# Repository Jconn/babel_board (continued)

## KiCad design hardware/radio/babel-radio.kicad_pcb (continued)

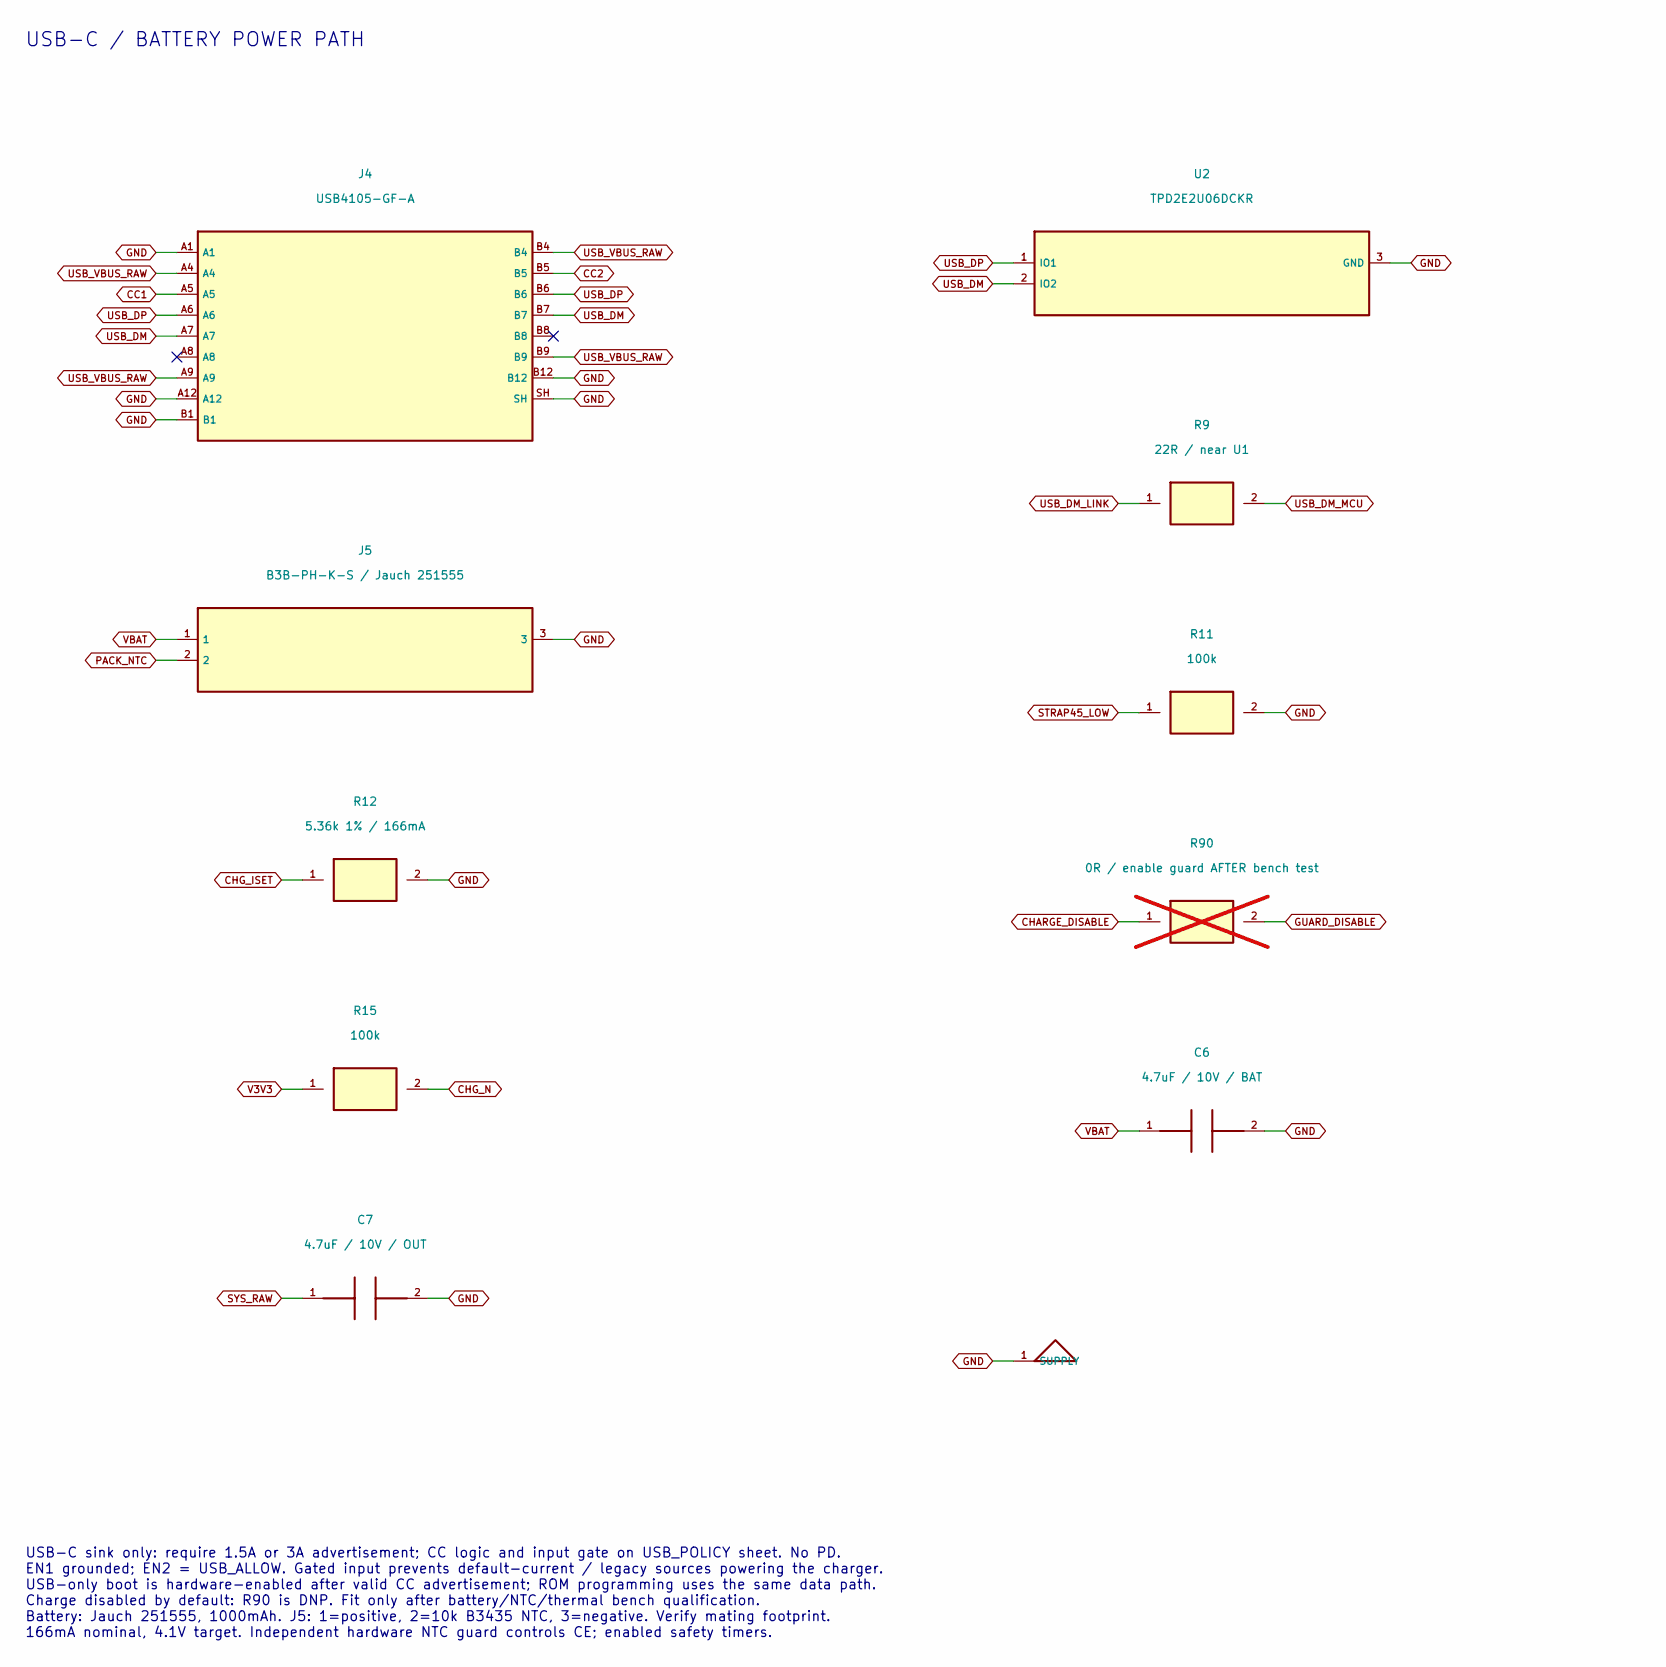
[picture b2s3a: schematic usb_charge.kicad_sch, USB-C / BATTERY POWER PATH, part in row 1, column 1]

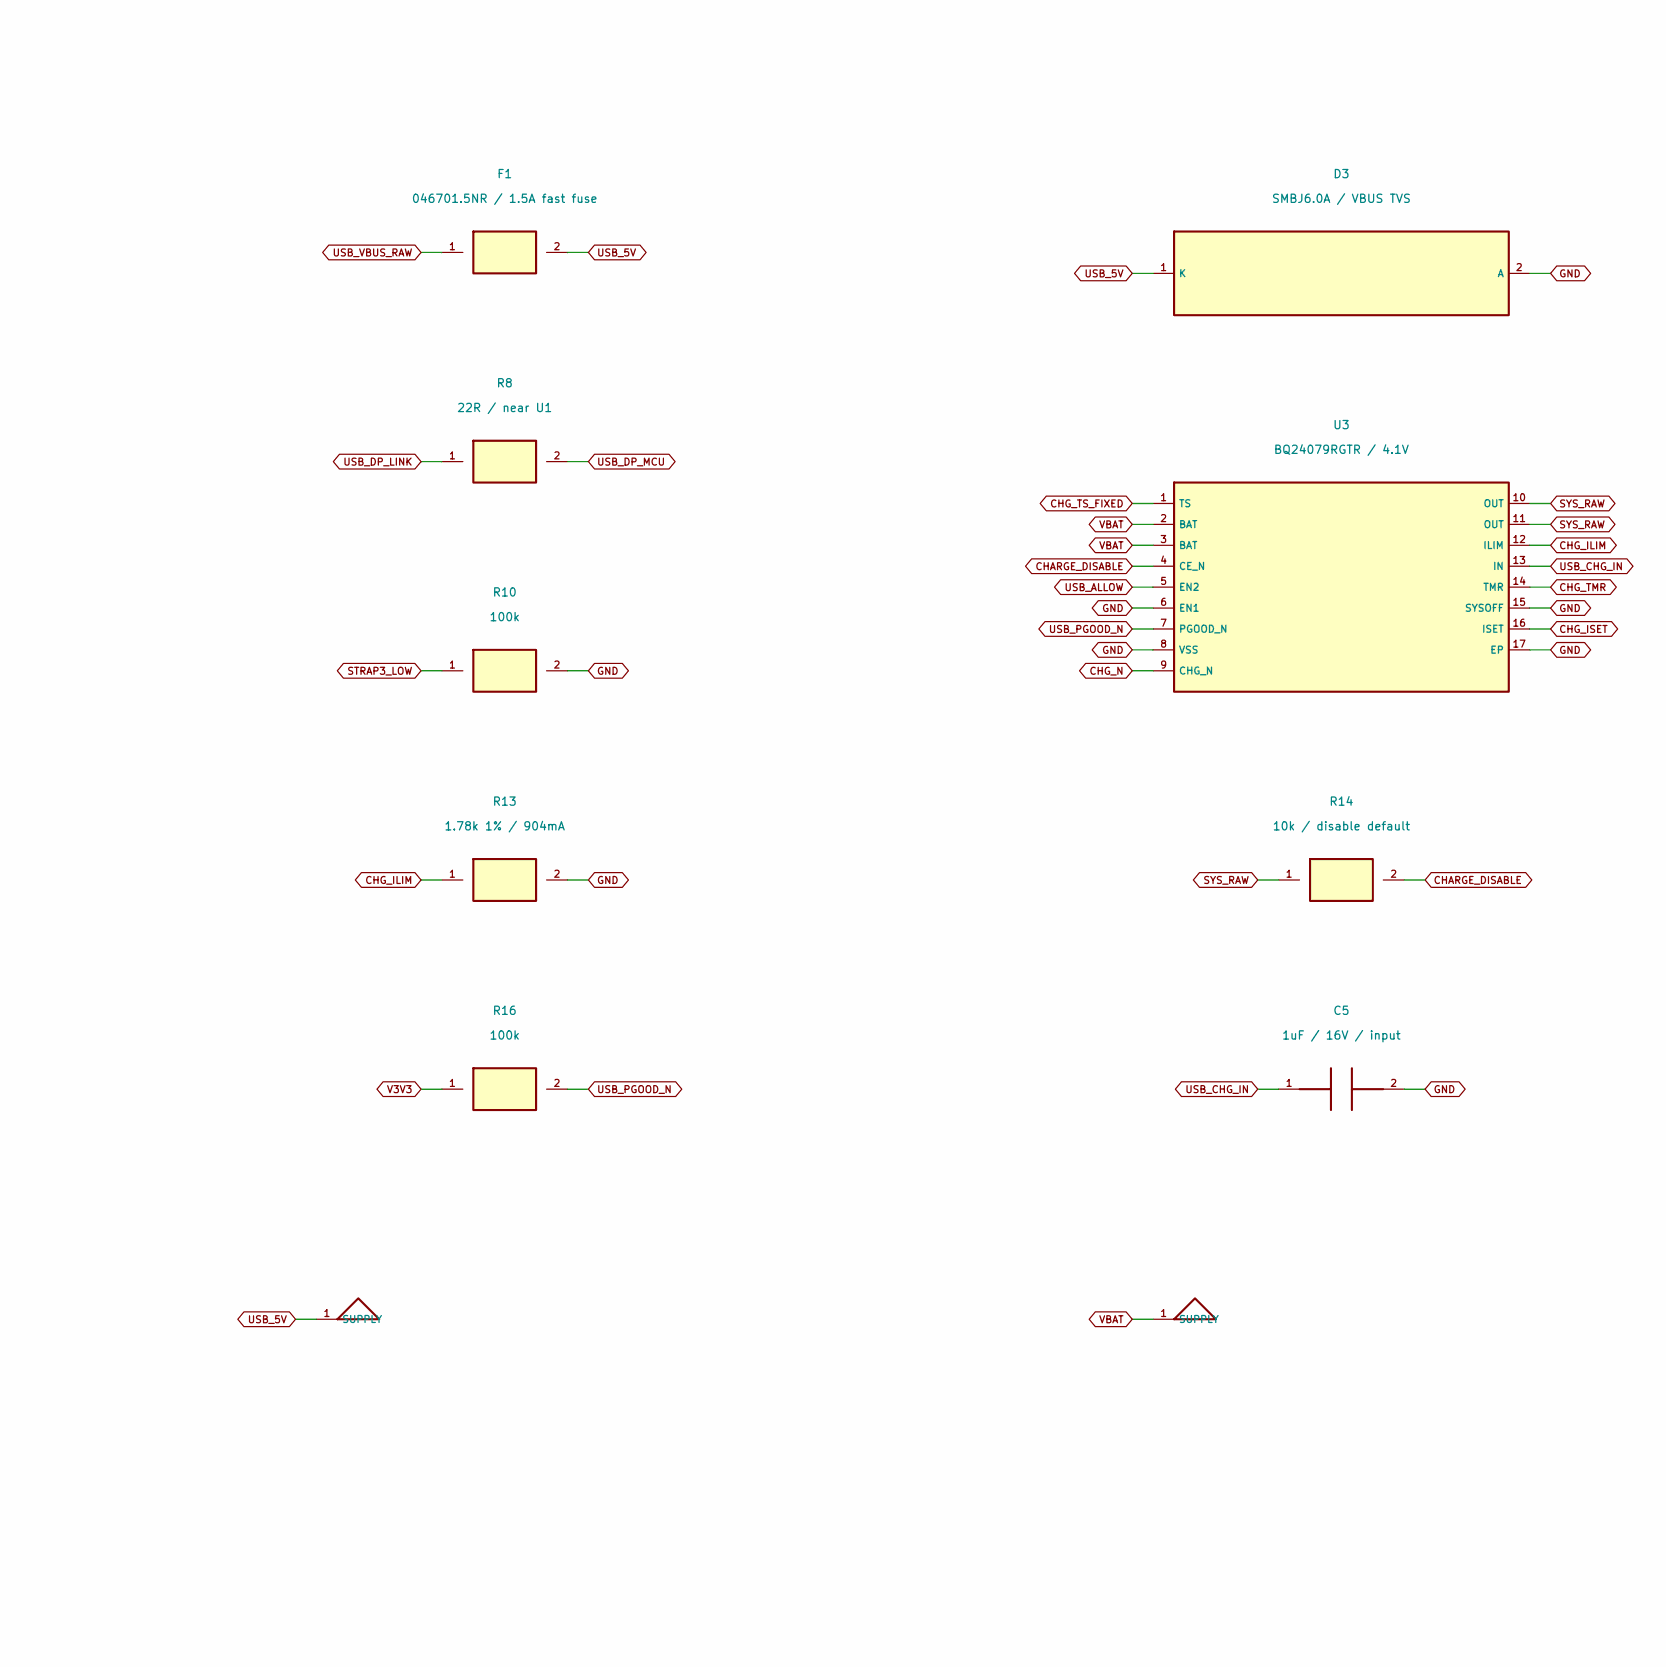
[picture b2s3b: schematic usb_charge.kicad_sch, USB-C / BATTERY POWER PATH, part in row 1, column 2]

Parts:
C5: 1uF / 16V / input; C_0805_2012Metric
C6: 4.7uF / 10V / BAT; C_0805_2012Metric
C7: 4.7uF / 10V / OUT; C_0805_2012Metric
D3: SMBJ6.0A / VBUS TVS; D_SMB; ManufacturerPartNumber SMBJ6.0A-13-F (Diodes Incorporated)
F1: 046701.5NR / 1.5A fast fuse; Fuse_0603_1608Metric
J4: USB4105-GF-A; USB_C_Receptacle_GCT_USB4105-xx-A_16P_TopMnt_Horizontal
J5: B3B-PH-K-S / Jauch 251555; JST_PH_B3B-PH-K_1x03_P2.00mm_Vertical
R8, R9: 22R / near U1; R_0603_1608Metric
R10, R11, R15, R16: 100k; R_0603_1608Metric
R12: 5.36k 1% / 166mA; R_0603_1608Metric
R13: 1.78k 1% / 904mA; R_0603_1608Metric
R14: 10k / disable default; R_0603_1608Metric
R90: 0R / enable guard AFTER bench test; R_0603_1608Metric; not fitted
U2: TPD2E2U06DCKR; SOT-323_SC-70
U3: BQ24079RGTR / 4.1V; BQ24079_RGT0016B

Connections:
CC1: J4.A5; also elsewhere on the board
CC2: J4.B5; also elsewhere on the board
CHARGE_DISABLE: R14.2, R90.1, U3.4 (CE_N); also elsewhere on the board
CHG_ILIM: R13.1, U3.12 (ILIM)
CHG_ISET: R12.1, U3.16 (ISET)
CHG_N: R15.2, U3.9 (CHG_N); also elsewhere on the board
CHG_TMR: U3.14 (TMR); also elsewhere on the board
CHG_TS_FIXED: U3.1 (TS); also elsewhere on the board
GND: C5.2, C6.2, C7.2, D3.2 (A), J4.A1, J4.A12, J4.B1, J4.B12, J4.SH, J5.3, R10.2, R11.2, R12.2, R13.2, U2.3 (GND), U3.6 (EN1), U3.8 (VSS), U3.15 (SYSOFF), U3.17 (EP); also elsewhere on the board
GUARD_DISABLE: R90.2; also elsewhere on the board
PACK_NTC: J5.2; also elsewhere on the board
STRAP3_LOW: R10.1; also elsewhere on the board
STRAP45_LOW: R11.1; also elsewhere on the board
SYS_RAW: C7.1, R14.1, U3.10 (OUT), U3.11 (OUT); also elsewhere on the board
USB_5V: D3.1 (K), F1.2; also elsewhere on the board
USB_ALLOW: U3.5 (EN2); also elsewhere on the board
USB_CHG_IN: C5.1, U3.13 (IN); also elsewhere on the board
USB_DM: J4.A7, J4.B7, U2.2 (IO2); also elsewhere on the board
USB_DM_LINK: R9.1; also elsewhere on the board
USB_DM_MCU: R9.2; also elsewhere on the board
USB_DP: J4.A6, J4.B6, U2.1 (IO1); also elsewhere on the board
USB_DP_LINK: R8.1; also elsewhere on the board
USB_DP_MCU: R8.2; also elsewhere on the board
USB_PGOOD_N: R16.2, U3.7 (PGOOD_N); also elsewhere on the board
USB_VBUS_RAW: F1.1, J4.A4, J4.A9, J4.B4, J4.B9
V3V3: R15.1, R16.1; also elsewhere on the board
VBAT: C6.1, J5.1, U3.2 (BAT), U3.3 (BAT); also elsewhere on the board

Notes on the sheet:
USB-C / BATTERY POWER PATH
USB-C sink only: require 1.5A or 3A advertisement; CC logic and input gate on USB_POLICY sheet. No PD. EN1 grounded; EN2 = USB_ALLOW. Gated input prevents default-current / legacy sources powering the charger. USB-only boot is hardware-enabled after valid CC advertisement; ROM programming uses the 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

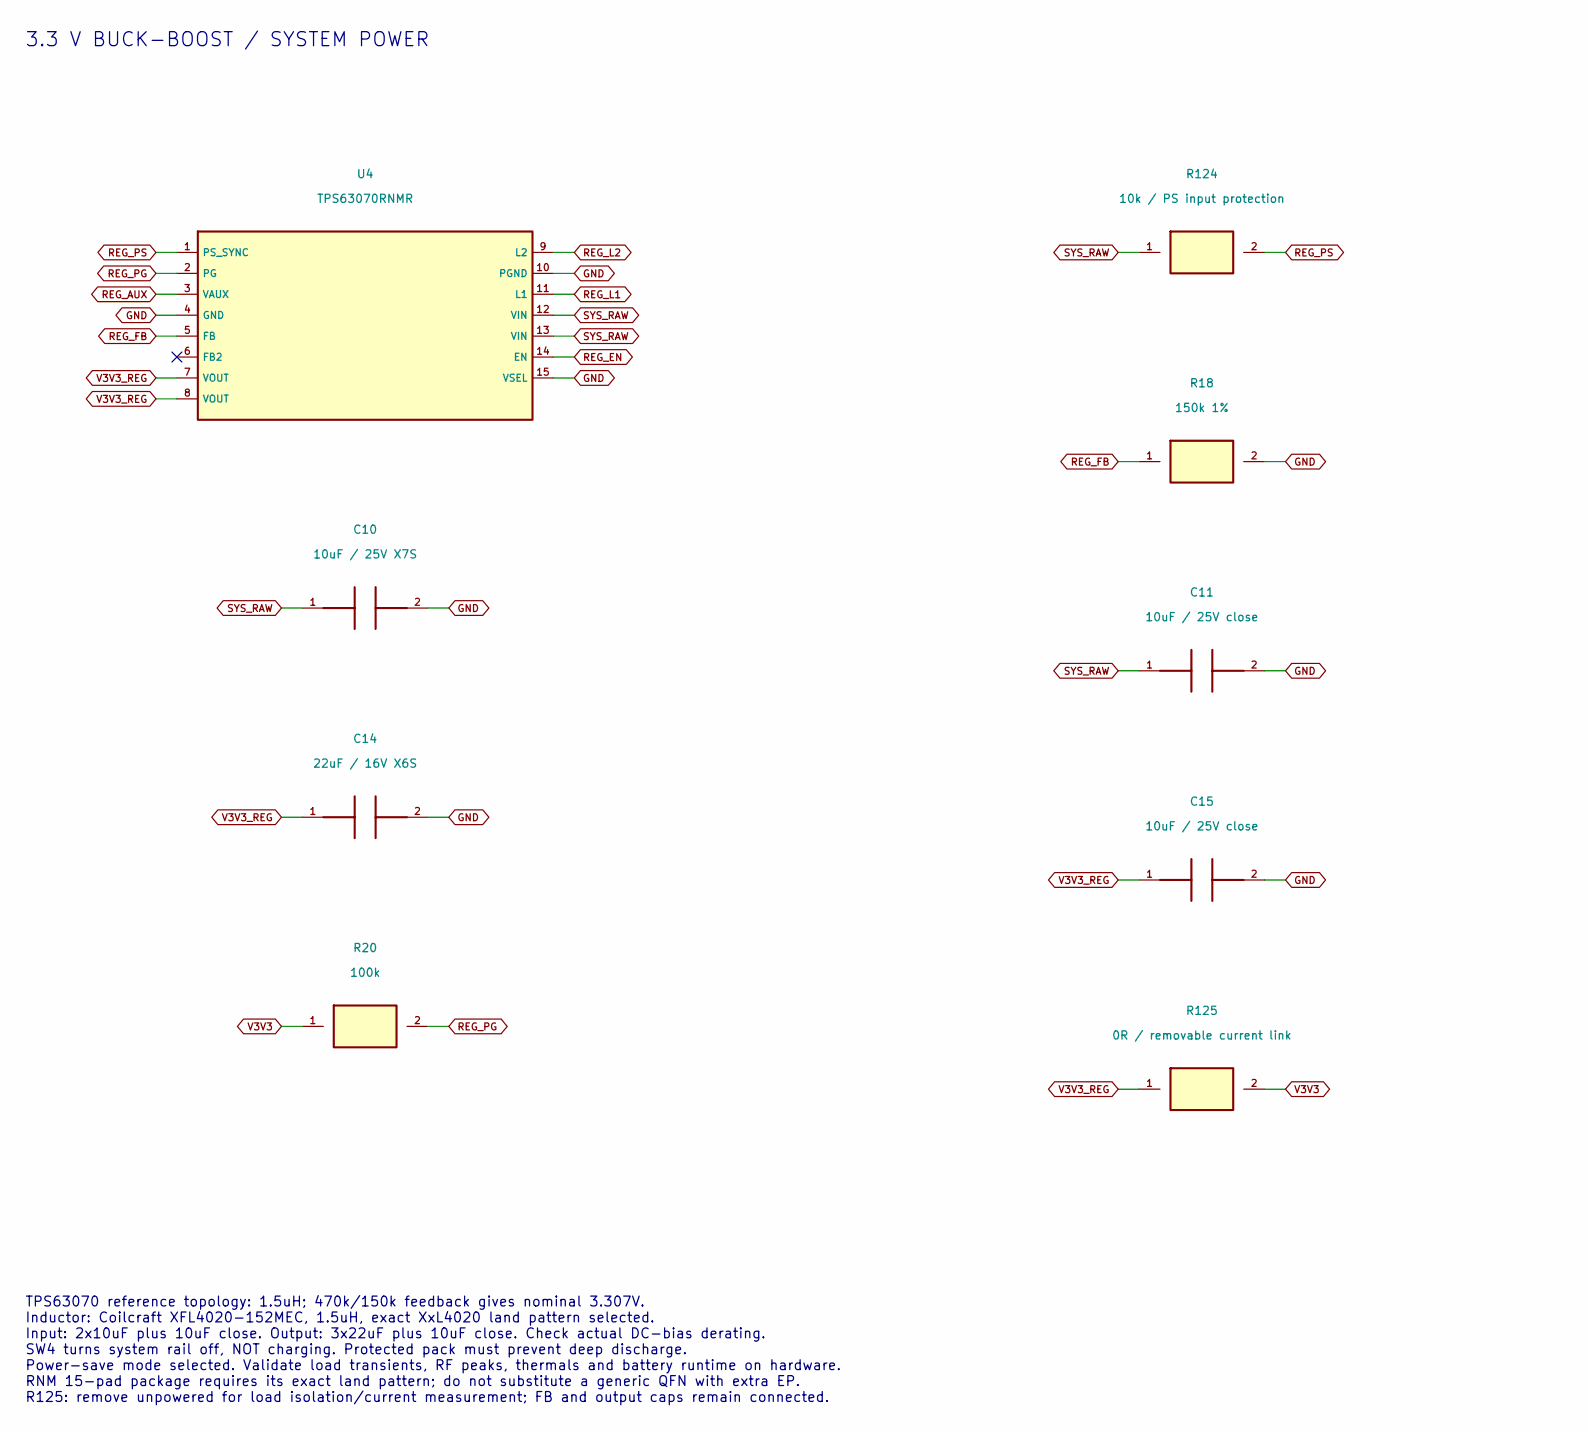
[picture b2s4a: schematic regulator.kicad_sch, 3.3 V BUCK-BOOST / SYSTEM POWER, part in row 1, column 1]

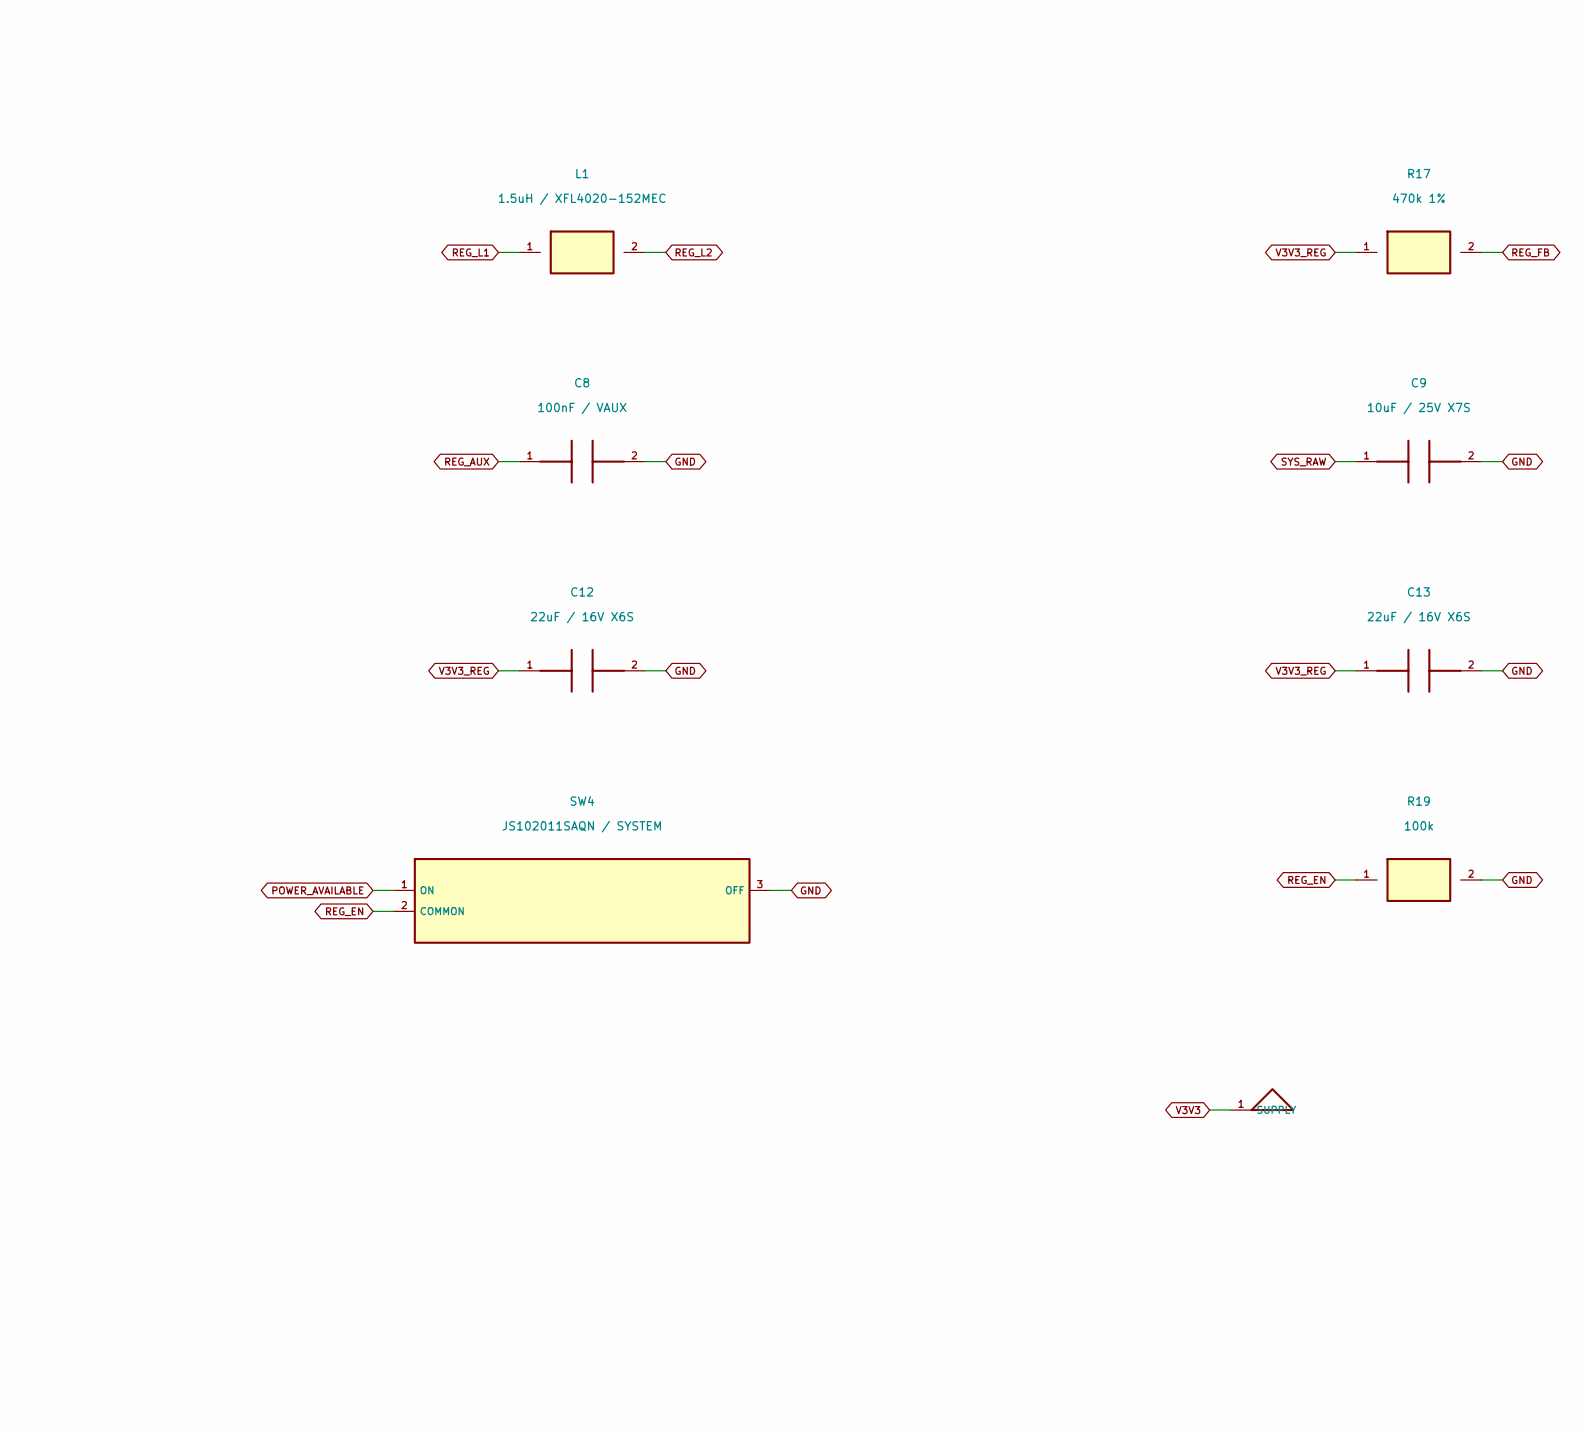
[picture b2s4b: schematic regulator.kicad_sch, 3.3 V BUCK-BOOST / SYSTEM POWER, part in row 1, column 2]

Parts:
C8: 100nF / VAUX; C_0805_2012Metric
C9, C10: 10uF / 25V X7S; C_0805_2012Metric; ManufacturerPartNumber GRM21BC71E106ME11L
C11, C15: 10uF / 25V close; C_0603_1608Metric; ManufacturerPartNumber TMK107BBJ106MA-T
C12, C13, C14: 22uF / 16V X6S; C_0805_2012Metric; ManufacturerPartNumber GRM21BC81C226ME44L
L1: 1.5uH / XFL4020-152MEC; L_Coilcraft_XxL4020
R17: 470k 1%; R_0603_1608Metric
R18: 150k 1%; R_0603_1608Metric
R19, R20: 100k; R_0603_1608Metric
R124: 10k / PS input protection; R_0603_1608Metric
R125: 0R / removable current link; R_0805_2012Metric
SW4: JS102011SAQN / SYSTEM; SW_SPDT_CK_JS102011SAQN
U4: TPS63070RNMR; TPS63070_RNM0015A

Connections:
GND: C8.2, C9.2, C10.2, C11.2, C12.2, C13.2, C14.2, C15.2, R18.2, R19.2, SW4.3 (OFF), U4.4 (GND), U4.10 (PGND), U4.15 (VSEL); also elsewhere on the board
POWER_AVAILABLE: SW4.1 (ON); also elsewhere on the board
REG_AUX: C8.1, U4.3 (VAUX)
REG_EN: R19.1, SW4.2 (COMMON), U4.14 (EN); also elsewhere on the board
REG_FB: R17.2, R18.1, U4.5 (FB)
REG_L1: L1.1, U4.11 (L1)
REG_L2: L1.2, U4.9 (L2)
REG_PG: R20.2, U4.2 (PG); also elsewhere on the board
REG_PS: R124.2, U4.1 (PS_SYNC)
SYS_RAW: C9.1, C10.1, C11.1, R124.1, U4.12 (VIN), U4.13 (VIN); also elsewhere on the board
V3V3: R20.1, R125.2; also elsewhere on the board
V3V3_REG: C12.1, C13.1, C14.1, C15.1, R17.1, R125.1, U4.7 (VOUT), U4.8 (VOUT); also elsewhere on the board

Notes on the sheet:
3.3 V BUCK-BOOST / SYSTEM POWER
TPS63070 reference topology: 1.5uH; 470k/150k feedback gives nominal 3.307V. Inductor: Coilcraft XFL4020-152MEC, 1.5uH, exact XxL4020 land pattern selected. Input: 2x10uF plus 10uF close. Output: 3x22uF plus 10uF close. Check actual DC-bias derating. SW4 turns system rail off, NOT charging. Protect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

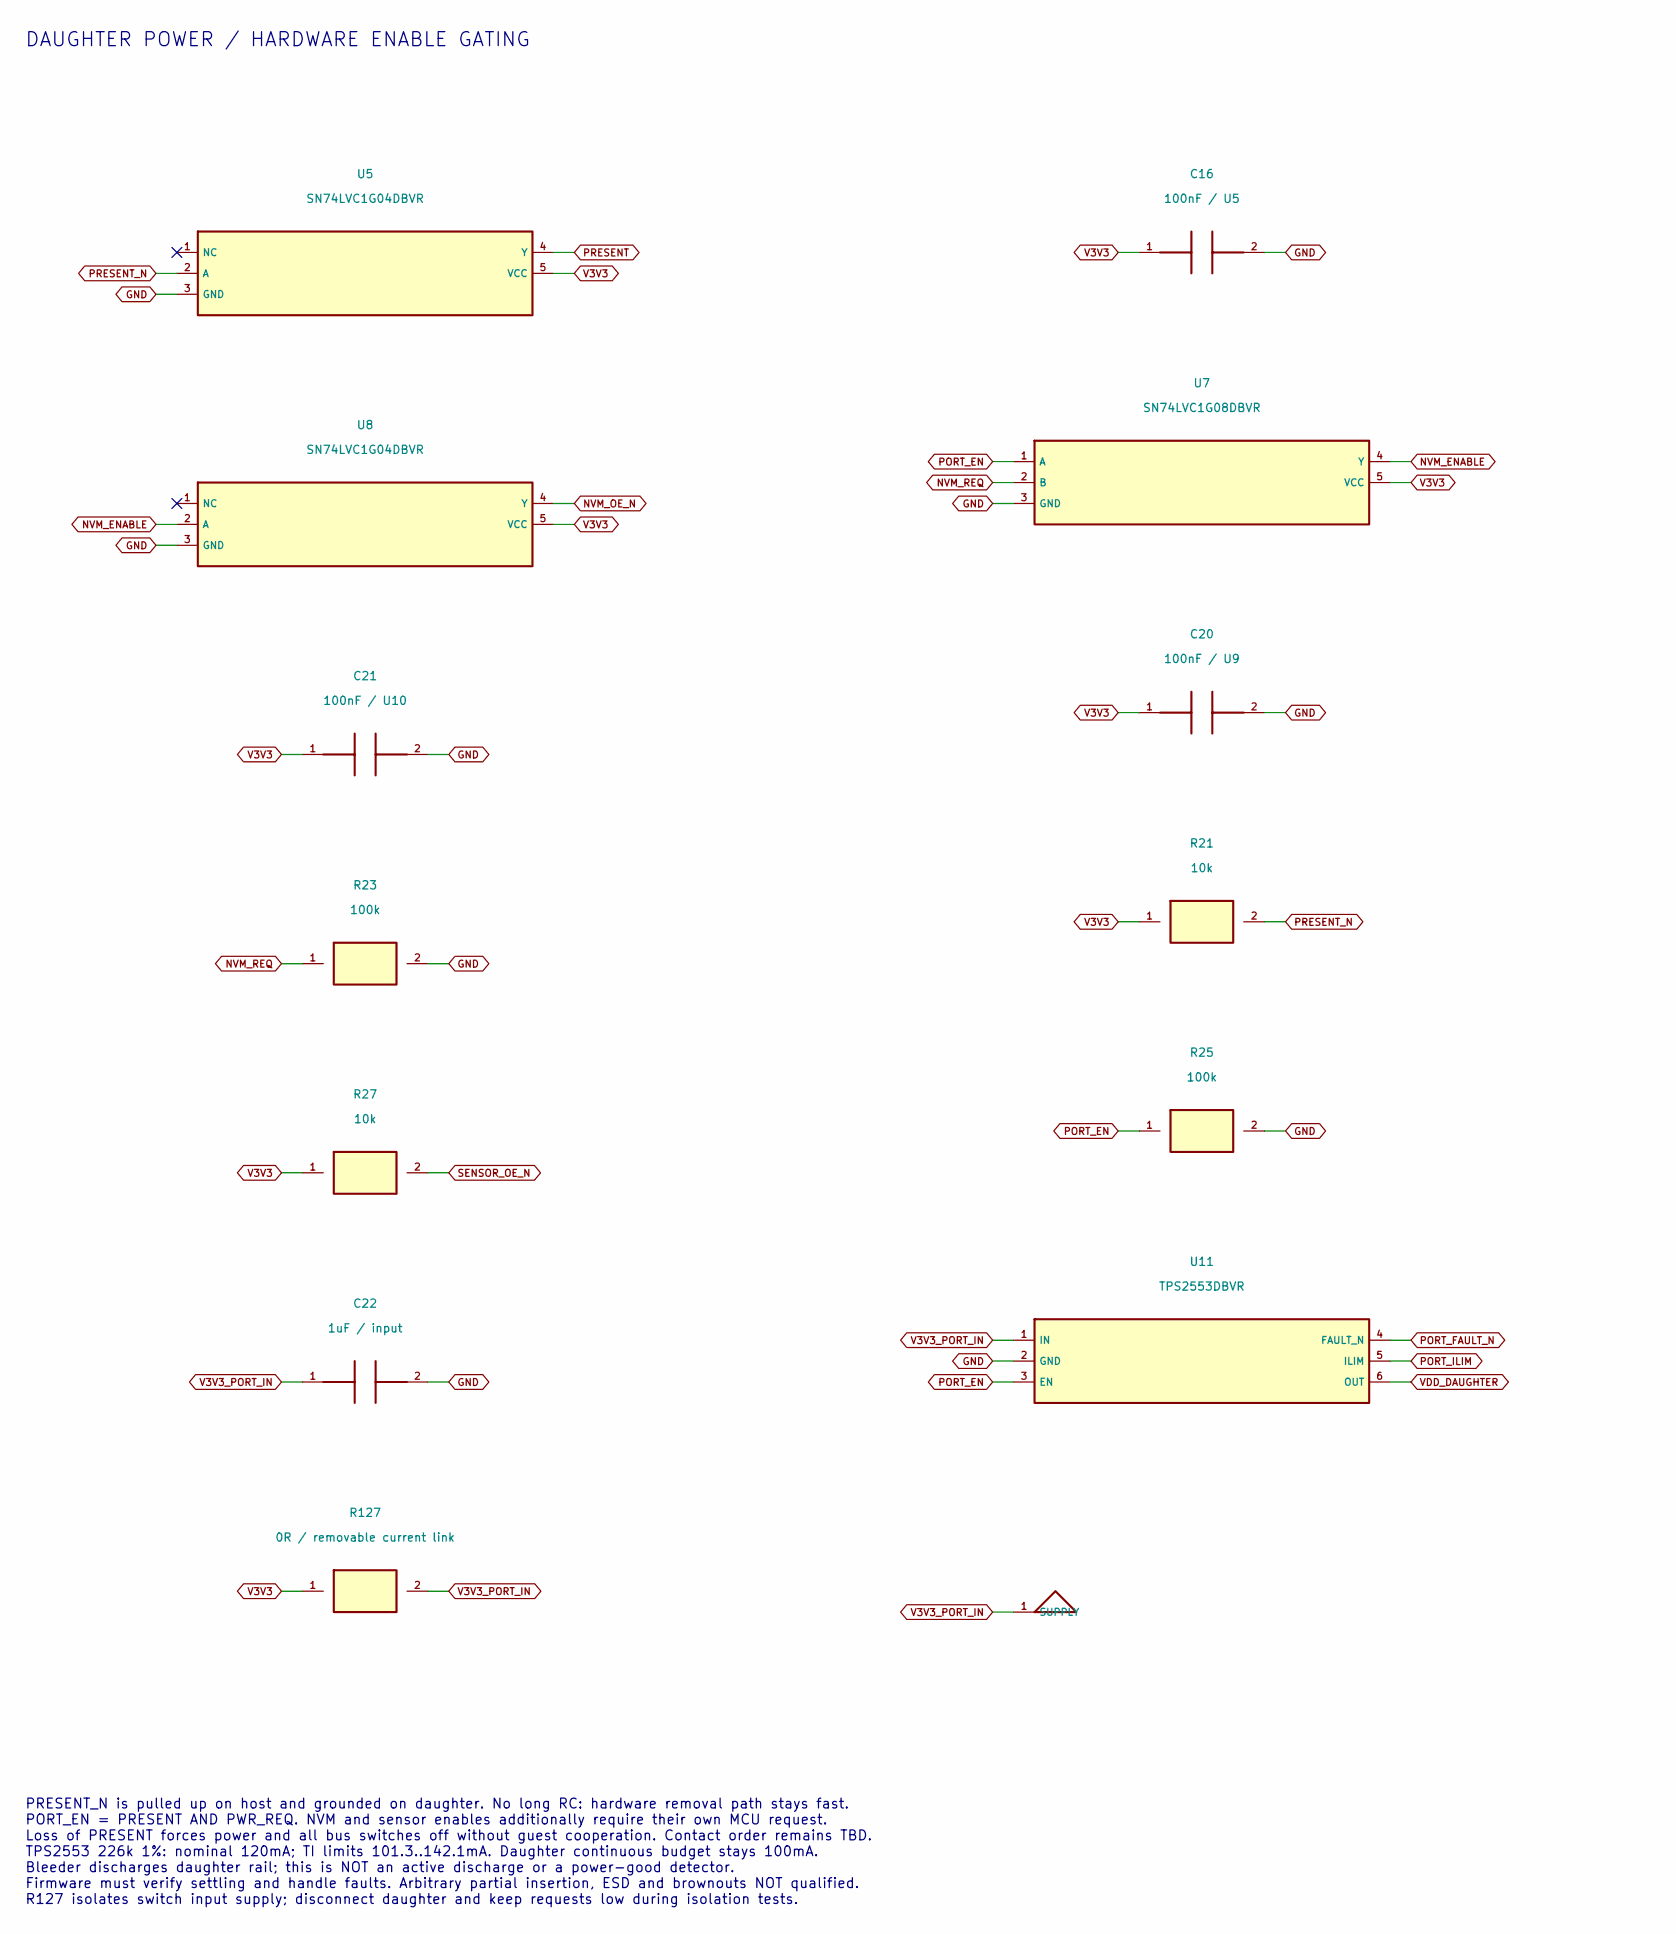
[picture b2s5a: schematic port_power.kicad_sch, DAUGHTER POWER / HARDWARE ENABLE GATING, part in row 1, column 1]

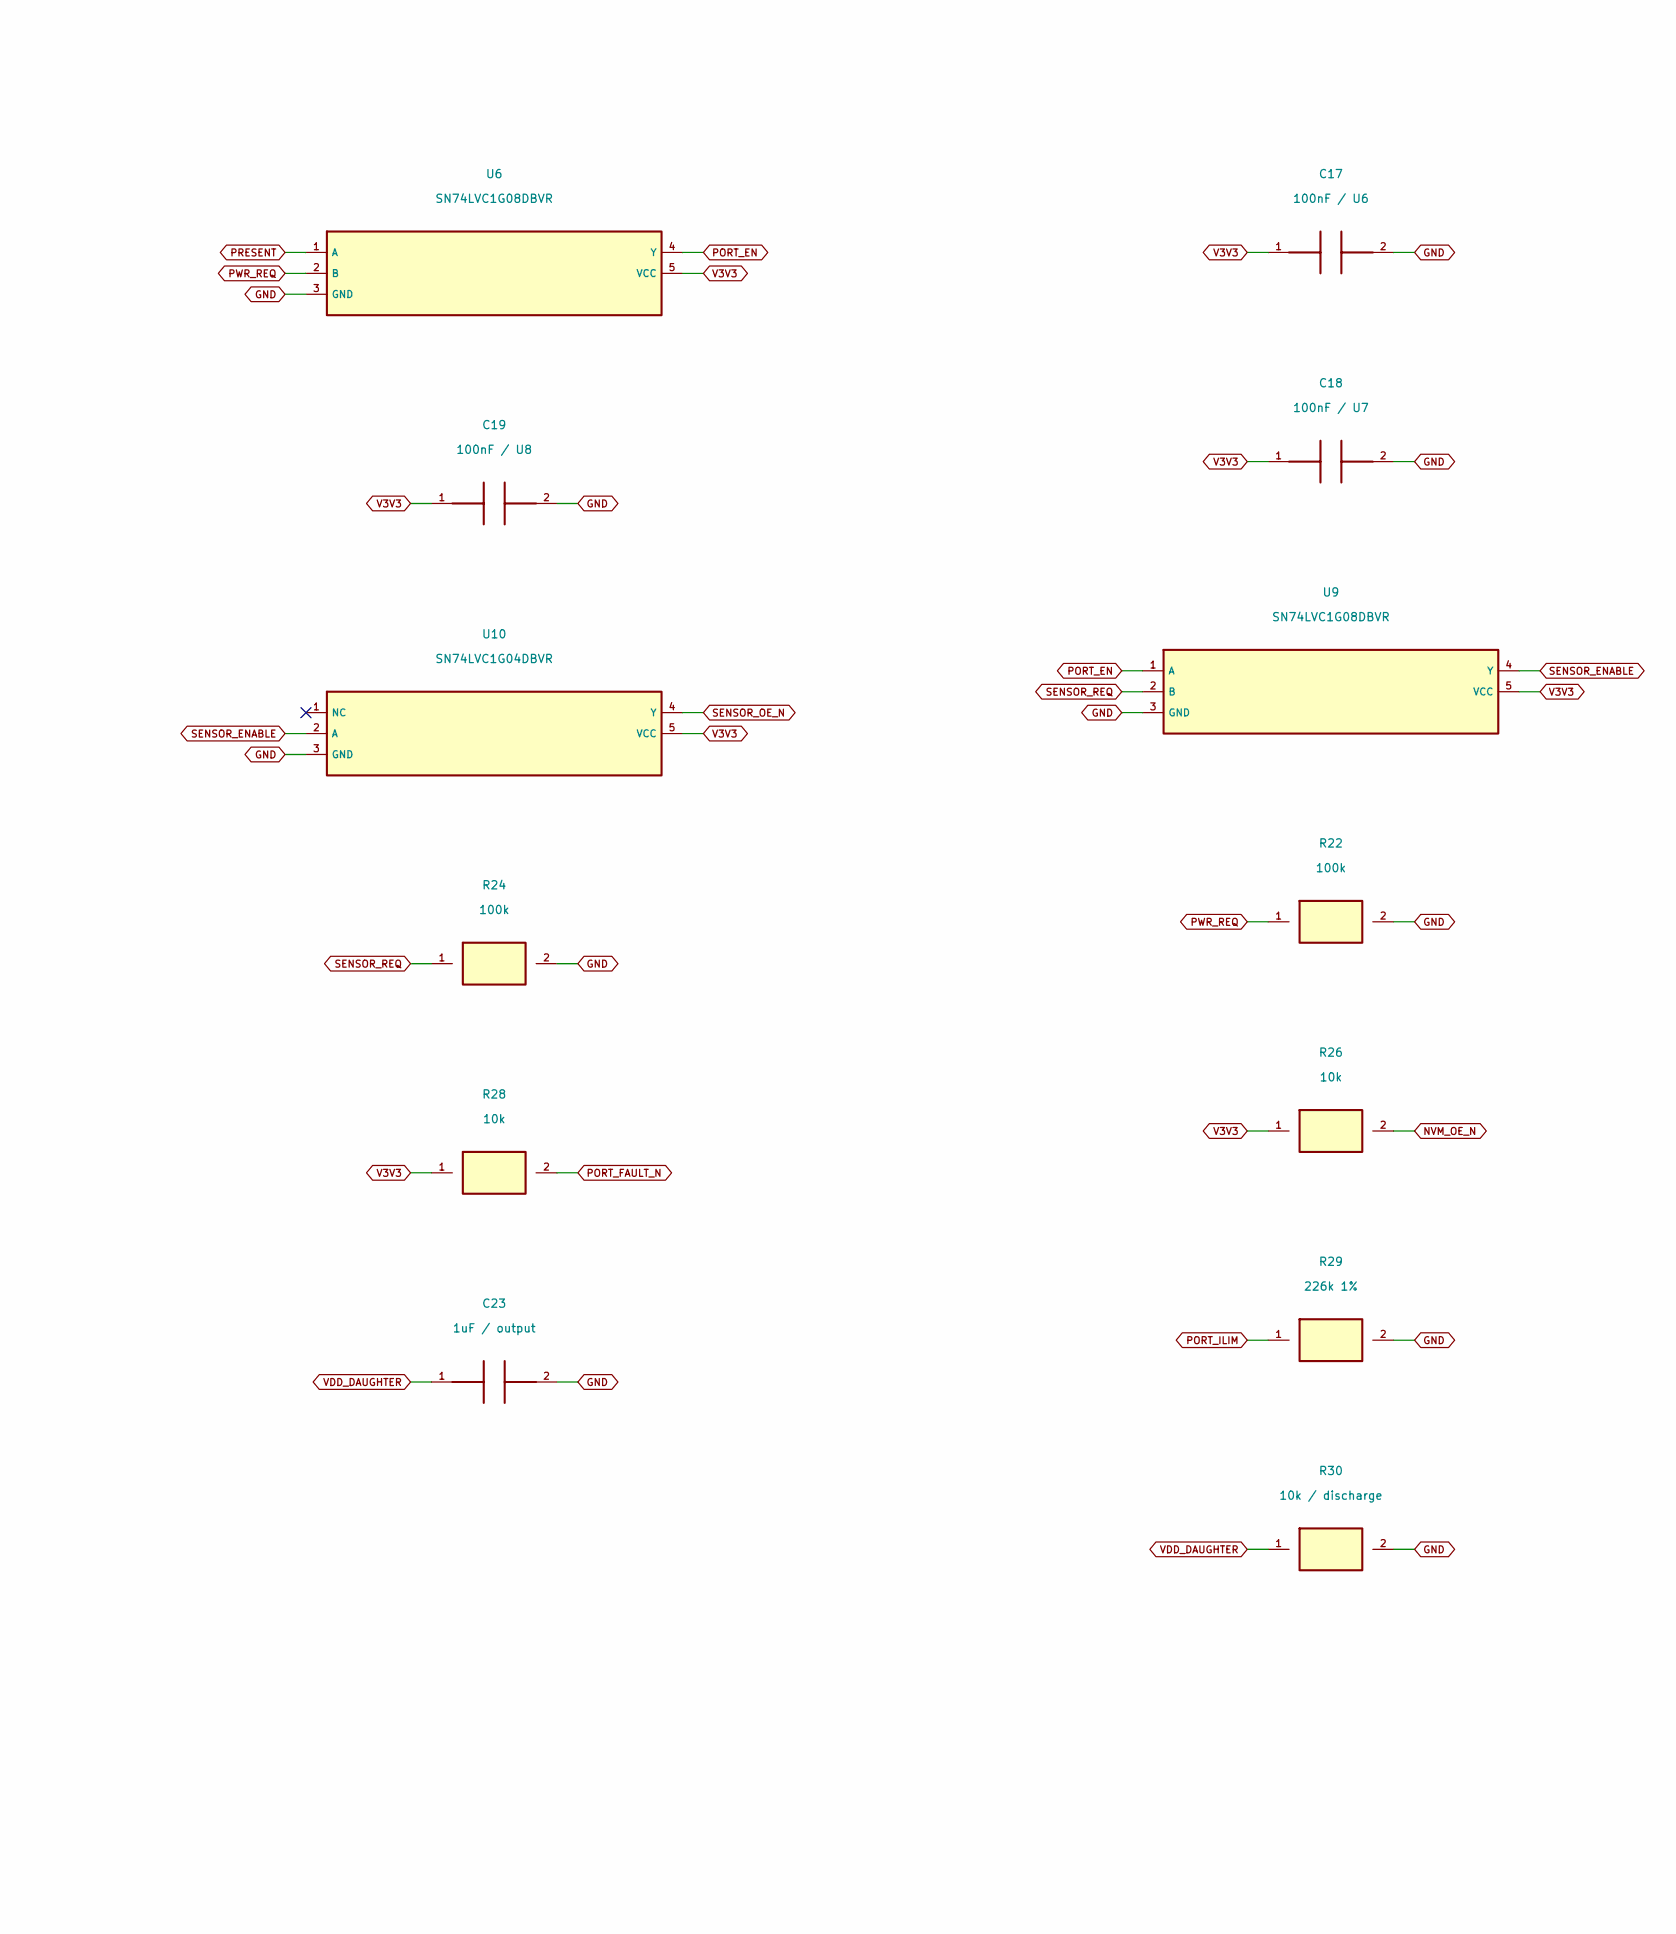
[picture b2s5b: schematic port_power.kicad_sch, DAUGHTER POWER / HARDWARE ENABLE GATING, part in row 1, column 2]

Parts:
C16: 100nF / U5; C_0805_2012Metric
C17: 100nF / U6; C_0805_2012Metric
C18: 100nF / U7; C_0805_2012Metric
C19: 100nF / U8; C_0805_2012Metric
C20: 100nF / U9; C_0805_2012Metric
C21: 100nF / U10; C_0805_2012Metric
C22: 1uF / input; C_0805_2012Metric
C23: 1uF / output; C_0805_2012Metric
R21, R26, R27, R28: 10k; R_0603_1608Metric
R22, R23, R24, R25: 100k; R_0603_1608Metric
R29: 226k 1%; R_0603_1608Metric
R30: 10k / discharge; R_0603_1608Metric
R127: 0R / removable current link; R_0603_1608Metric
U5, U8, U10: SN74LVC1G04DBVR; SOT-23-5
U6, U7, U9: SN74LVC1G08DBVR; SOT-23-5
U11: TPS2553DBVR; SOT-23-6

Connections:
GND: C16.2, C17.2, C18.2, C19.2, C20.2, C21.2, C22.2, C23.2, R22.2, R23.2, R24.2, R25.2, R29.2, R30.2, U5.3 (GND), U6.3 (GND), U7.3 (GND), U8.3 (GND), U9.3 (GND), U10.3 (GND), U11.2 (GND); also elsewhere on the board
NVM_ENABLE: U7.4 (Y), U8.2 (A)
NVM_OE_N: R26.2, U8.4 (Y); also elsewhere on the board
NVM_REQ: R23.1, U7.2 (B); also elsewhere on the board
PORT_EN: R25.1, U6.4 (Y), U7.1 (A), U9.1 (A), U11.3 (EN); also elsewhere on the board
PORT_FAULT_N: R28.2, U11.4 (FAULT_N); also elsewhere on the board
PORT_ILIM: R29.1, U11.5 (ILIM)
PRESENT: U5.4 (Y), U6.1 (A)
PRESENT_N: R21.2, U5.2 (A); also elsewhere on the board
PWR_REQ: R22.1, U6.2 (B); also elsewhere on the board
SENSOR_ENABLE: U9.4 (Y), U10.2 (A)
SENSOR_OE_N: R27.2, U10.4 (Y); also elsewhere on the board
SENSOR_REQ: R24.1, U9.2 (B); also elsewhere on the board
V3V3: C16.1, C17.1, C18.1, C19.1, C20.1, C21.1, R21.1, R26.1, R27.1, R28.1, R127.1, U5.5 (VCC), U6.5 (VCC), U7.5 (VCC), U8.5 (VCC), U9.5 (VCC), U10.5 (VCC); also elsewhere on the board
V3V3_PORT_IN: C22.1, R127.2, U11.1 (IN)
VDD_DAUGHTER: C23.1, R30.1, U11.6 (OUT); also elsewhere on the board

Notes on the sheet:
DAUGHTER POWER / HARDWARE ENABLE GATING
PRESENT_N is pulled up on host and grounded on daughter. No long RC: hardware removal path stays fast. PORT_EN = PRESENT AND PWR_REQ. NVM and sensor enables additionally require their own MCU request. Loss of PRESENT forces power and all bus switches off without guest cooperation. Contact order rem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
